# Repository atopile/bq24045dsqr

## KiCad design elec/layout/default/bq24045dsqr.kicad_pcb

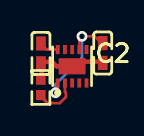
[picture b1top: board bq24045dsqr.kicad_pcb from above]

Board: 2 copper layers, 4 parts (0 on the bottom side), 4 nets.

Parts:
C1, C2: 1µF ±10% 25V X5R; C0402-b3ef17
R1: 560Ω ±1% 62.5mW; R0402-56259e
U1: WSON-10_L2.0-W2.0-P0.40-BL-EP

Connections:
IN: C1.1, U1.1, U1.7
ISET: R1.1, U1.2
OUT: C2.1, U1.10
gnd: C1.2, C2.2, R1.2, U1.3, U1.11

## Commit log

2024-02-16 Configure project
2024-02-17 initial layout
2024-02-17 add layout
2024-02-29 updated with equations
2024-03-08 update layout
2024-03-08 commenting out default resistor value
2024-03-10 added config for different battery voltage chips
2024-07-05 Remove crud from layout
2025-03-06 remove old component server from ato.yaml
2025-03-06 updated to newest ato syntax, rearanged equations for solver
2025-03-06 add code-workspace to gitignore
2025-04-05 update to kicad 9
2025-04-05 build with latest
